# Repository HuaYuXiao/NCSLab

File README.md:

#  NCSLab 

## Installation

- Install [`Node.js`](https://nodejs.org/en/download/package-manager)

- Install [`three.js`](https://threejs.org/docs/index.html#manual/en/introduction/Installation) and a build tool [`Vite`](https://threejs.org/docs/index.html#manual/en/introduction/Installation)

## Launch

```bash
cd ~/NCSLab/workspace
python3 main.py
python3 mjpeg_server.py
```

### PWM波控制可变电源

输出电压与PWM波占空比关系如下：

参考：
- [PWM原理 PWM频率与占空比详解](https://blog.csdn.net/as480133937/article/details/103439546)

输出电流稳定在20mA。

## Picamera2

update:2024.6.14
下面这个方案已废弃

update:2024.5.17
先运行/src/online/Camera_test/server_camera.py 在localhost:8091/video_feed下开启视频流
然后/src/online/main.py 运行主网页

Reference
- ⭐️ https://github.com/barry-ran/raspberry-webcam
- ⭐️ [How to Install & Setup OpenCV on Raspberry Pi 4](https://how2electronics.com/how-to-install-setup-opencv-on-raspberry-pi-4)
- ⭐️ https://github.com/raspberrypi/picamera2/blob/main/examples/preview.py
- [Installing OpenCV on Raspberry Pi 4B](https://www.youtube.com/watch?v=OugQIz_vcFo)

## 识别电压电流数据

测试图片如下：

注意到，底色和内容颜色都是单一的，因此我们首先通过二值化将两者分离开来。

## Release Note

- v2.1.4:
    - fix issue #11 #12 #19
- v2.1.3: 
    - self defined `html` & `js`
- v2.1.2:
  - `rectangle-module` and `submit`
- v2.1.1:
  - support video streaming
- v2.1.0: 
  - support continuous channel switch
  - support check for invalid input

## Contributor
- Circuit Design: Xizhe Hao, Hongjin Tang
- Video Promotion：Zixuan zhong， Yuxiao Hua
- Web Design： Yuxiao Hua
- Patent Drafting: Yuxiao Hua, Xizhe Hao, Yifeng Zhang
- Patent Application:Xizhe Hao, Yuxiao Hua

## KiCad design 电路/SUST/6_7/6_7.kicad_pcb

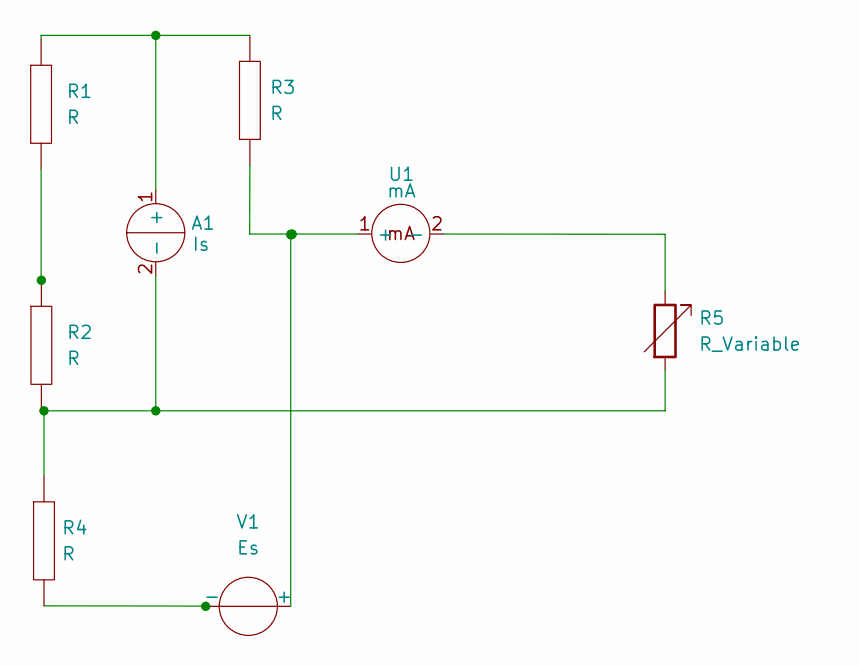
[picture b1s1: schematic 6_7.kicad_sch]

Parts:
A1: Is
R1, R2, R3, R4: R
R5: R_Variable; Rv
U1: mA; Multimeter
V1: Es; Vs

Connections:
unnamed: A1.1 (+), R1.1, R3.1
unnamed: A1.2 (-), R2.2, R4.1, R5.2
unnamed: R1.2, R2.1
unnamed: R3.2, U1.1 (+), V1.1 (+)
unnamed: R4.2, V1.2 (-)
unnamed: R5.1, U1.2 (-)

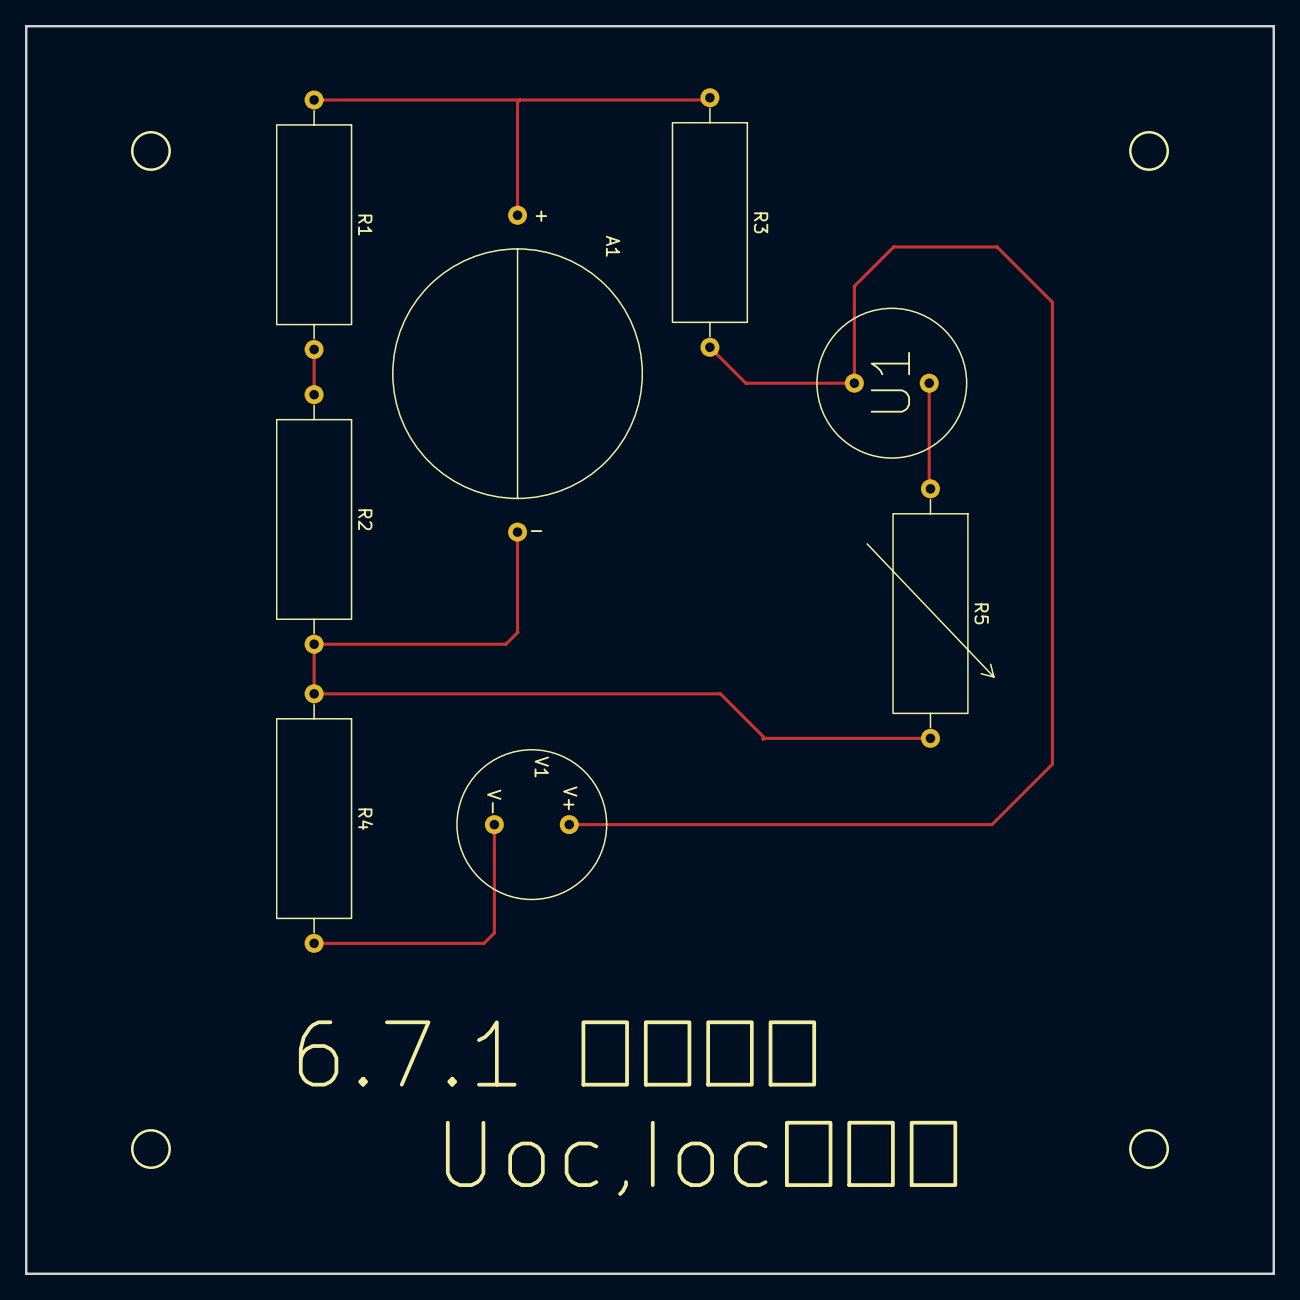
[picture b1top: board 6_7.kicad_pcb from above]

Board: 2 copper layers, 100.0 x 100.0 mm, 8 parts (0 on the bottom side), 6 nets.

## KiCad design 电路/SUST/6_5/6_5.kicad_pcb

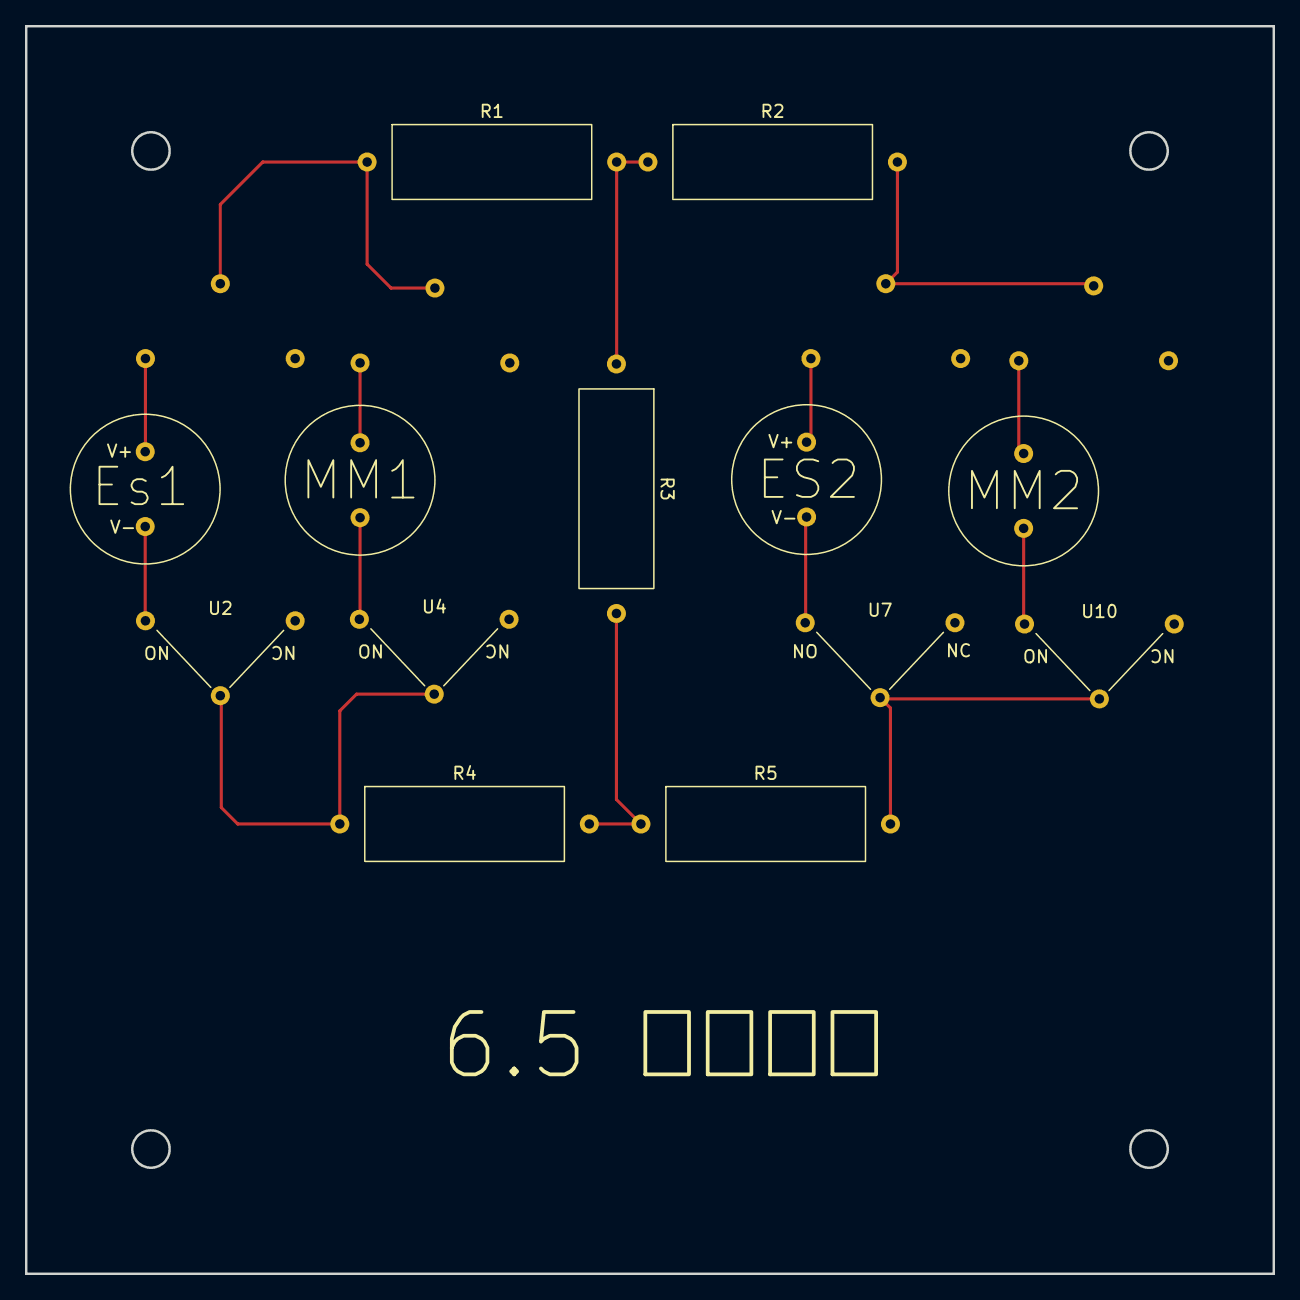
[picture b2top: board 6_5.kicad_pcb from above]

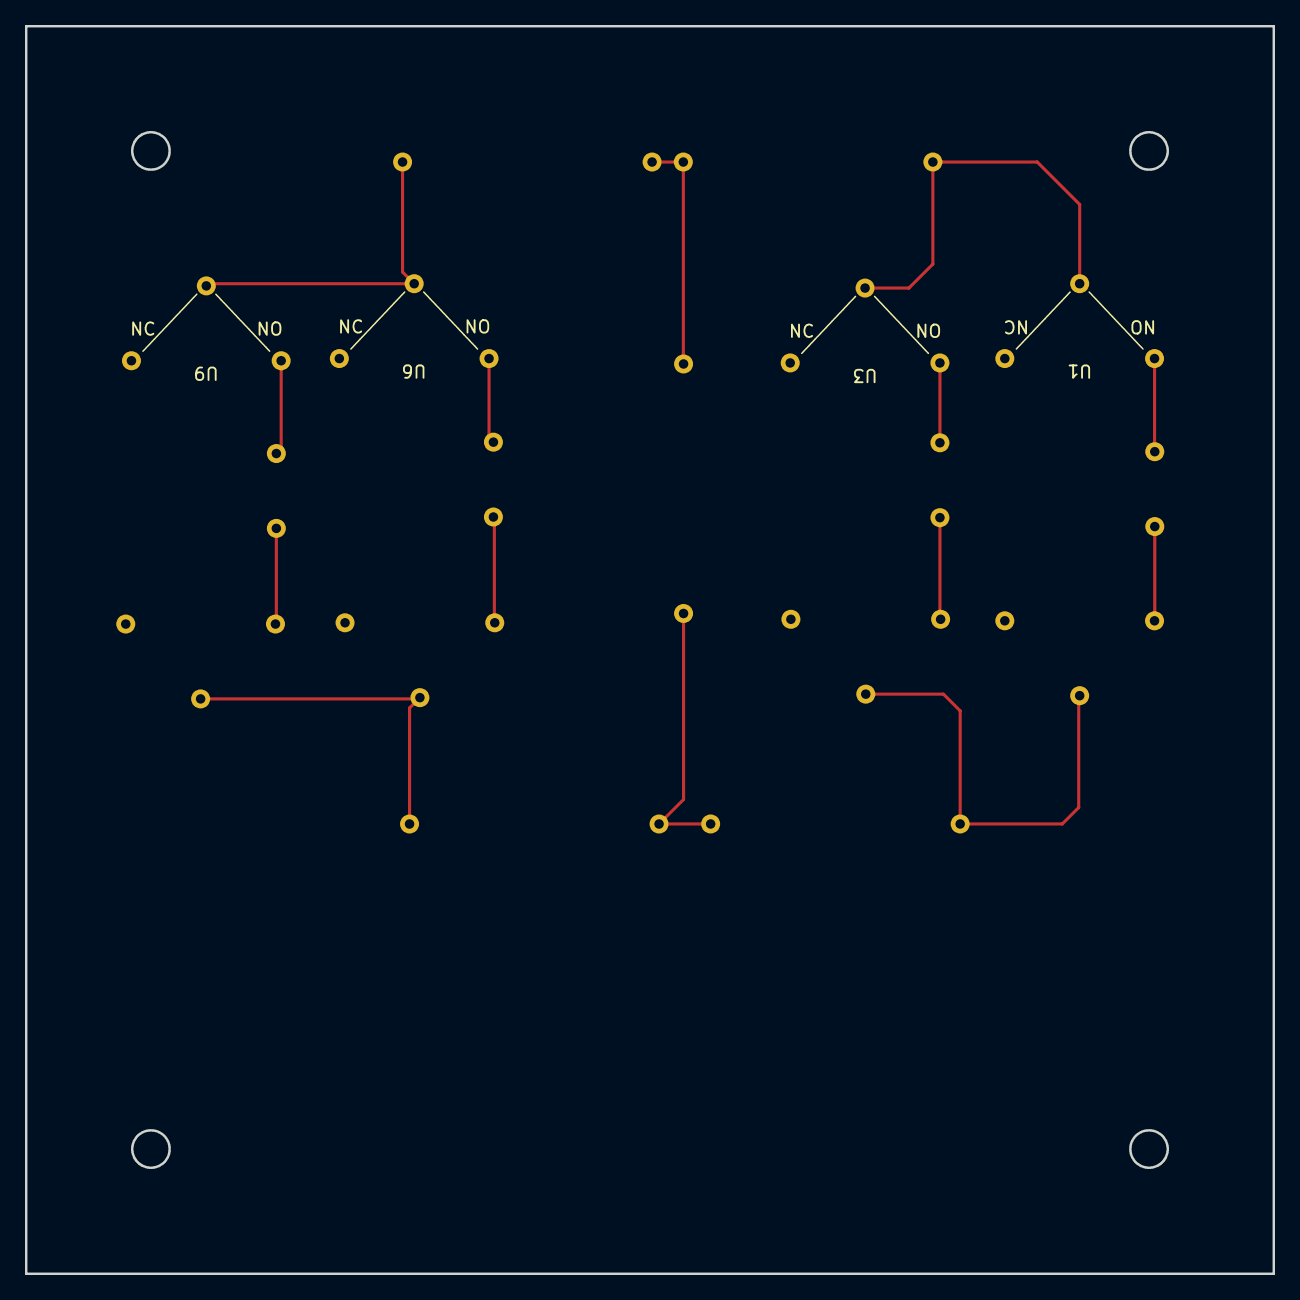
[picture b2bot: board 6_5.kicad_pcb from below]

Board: 2 copper layers, 100.0 x 100.0 mm, 17 parts (4 on the bottom side), 14 nets.

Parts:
ES2: Es; Vs
Es1: Es; Vs
MM1, MM2: Multimeter
R1, R3, R4: 510Ω; R
R2: 1kΩ; R
R5: 300Ω; R
U1, U2, U3, U4, U6, U7, U9, U10: Rly; RLy

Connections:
unnamed: R1.1, U1.1 (Com), U3.1 (Com)
unnamed: R1.2, R2.1, R3.1
unnamed: R2.2, U6.1 (Com), U9.1 (Com)
unnamed: R4.1, U2.1 (Com), U4.1 (Com)
unnamed: R3.2, R4.2, R5.1
unnamed: R5.2, U7.1 (Com), U10.1 (Com)
unnamed: Es1.1 (+), U1.3 (NO)
unnamed: Es1.2 (-), U2.3 (NO)
unnamed: MM1.1 (+), U3.3 (NO)
unnamed: MM1.2 (-), U4.3 (NO)
unnamed: ES2.1 (+), U6.3 (NO)
unnamed: ES2.2 (-), U7.3 (NO)
unnamed: MM2.1 (+), U9.3 (NO)
unnamed: MM2.2 (-), U10.3 (NO)

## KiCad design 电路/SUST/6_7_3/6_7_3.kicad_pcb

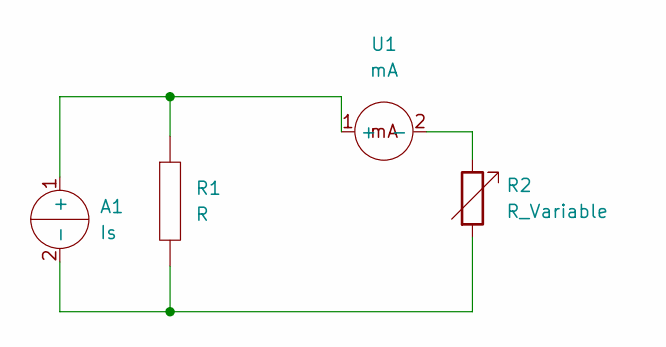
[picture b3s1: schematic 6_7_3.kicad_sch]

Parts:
A1: Is
R1: R
R2: R_Variable; Rv
U1: mA; Multimeter

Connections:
unnamed: A1.1 (+), R1.1, U1.1 (+)
unnamed: A1.2 (-), R1.2, R2.2
unnamed: R2.1, U1.2 (-)

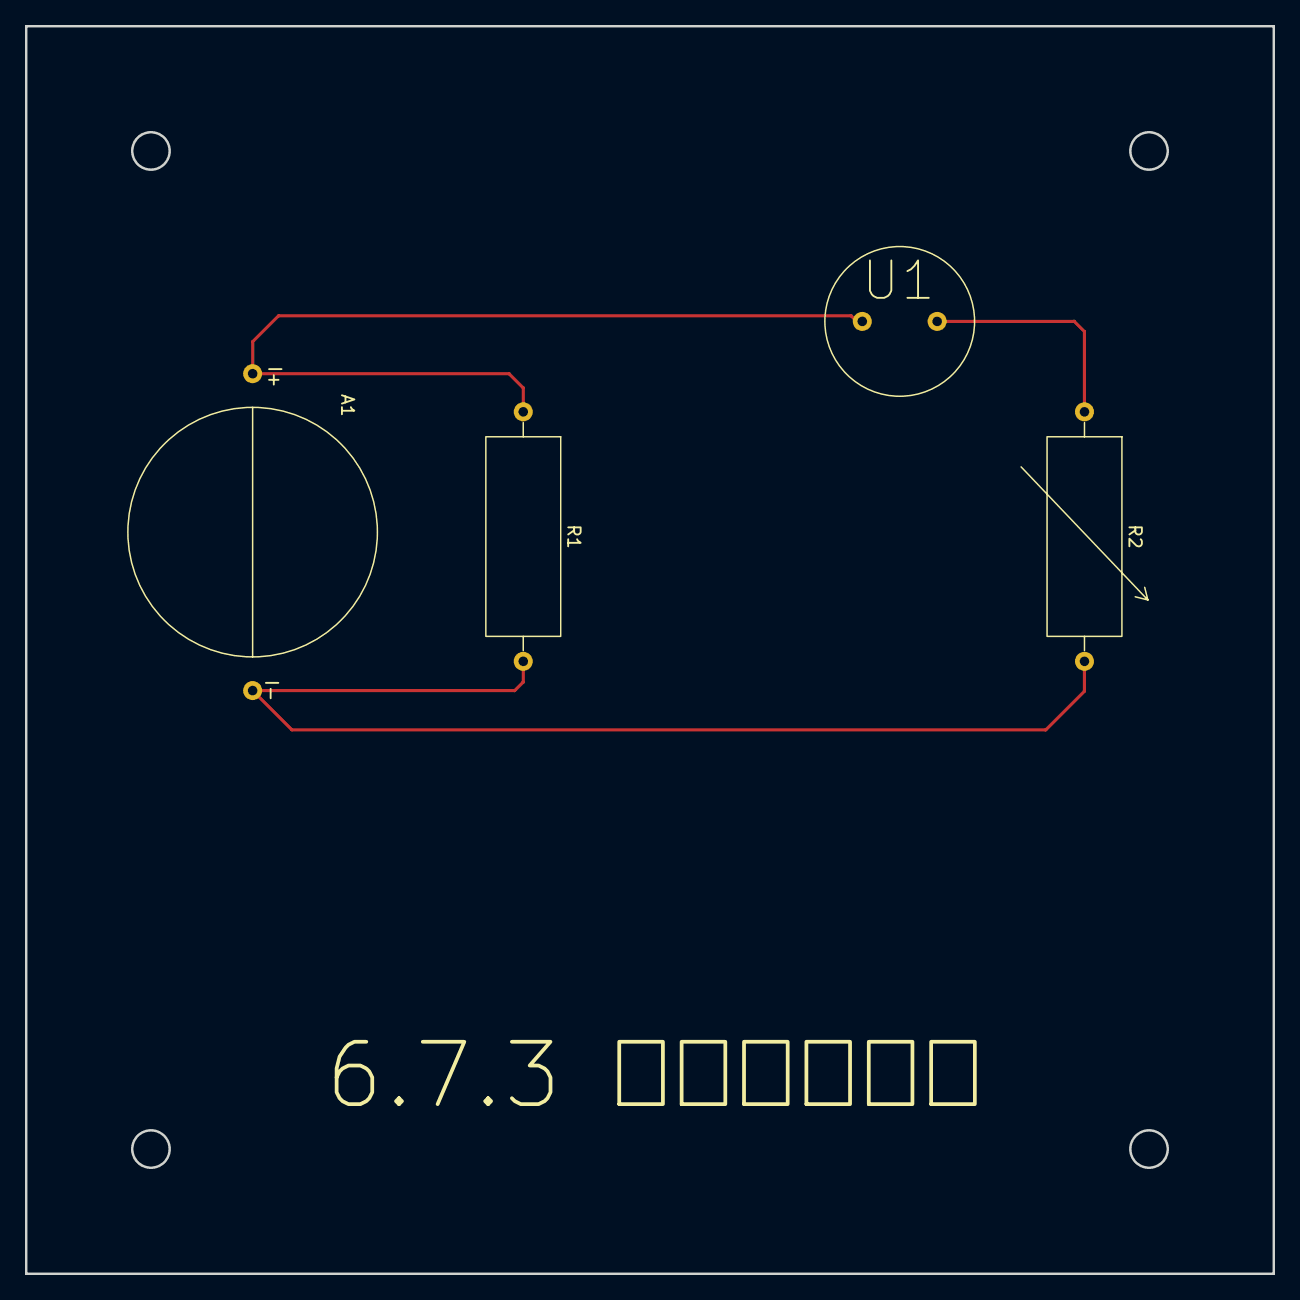
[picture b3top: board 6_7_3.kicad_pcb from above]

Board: 2 copper layers, 100.0 x 100.0 mm, 4 parts (0 on the bottom side), 3 nets.

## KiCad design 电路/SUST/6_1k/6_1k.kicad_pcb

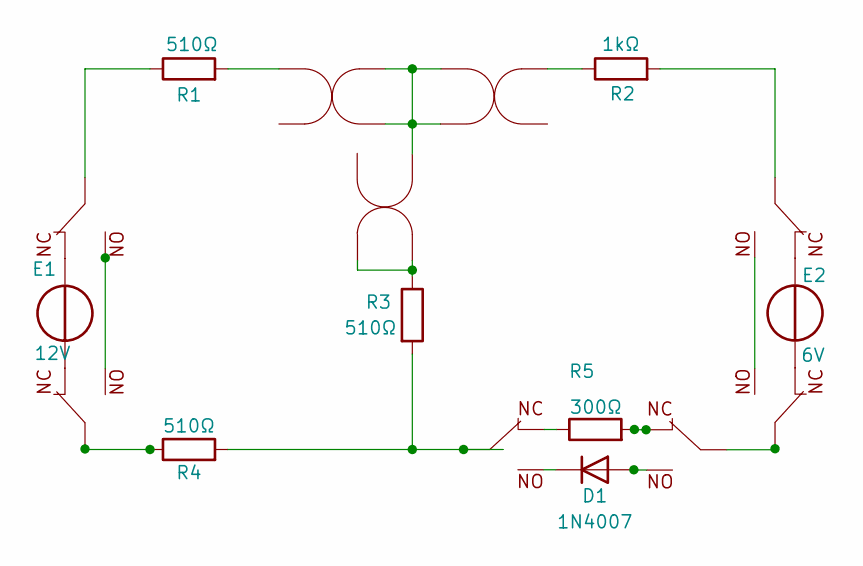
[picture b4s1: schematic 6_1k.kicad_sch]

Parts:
D1: 1N4007; D_DO-41_SOD81_P10.16mm_Horizontal
E1: 12V; Vs
E2: 6V; Vs
P1, P2, P3: AmPlug; ImaPlug
R1, R3, R4: 510Ω; R
R2: 1kΩ; R
R5: 300Ω; R
Rl1, Rl2, Rl3, Rl4, Rl5, Rl6: Relay; RLy

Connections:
unnamed: D1.2 (A), Rl2.3 (NO)
unnamed: E1.1 (V+), Rl3.2 (NC)
unnamed: E1.2 (V-), Rl4.2 (NC)
unnamed: E2.1 (V+), Rl5.3 (NC)
unnamed: E2.2 (V-), Rl6.3 (NC)
unnamed: P1.1, R1.2
unnamed: P1.3, P1.4, P2.3, P2.4, P3.3
unnamed: P2.1, R2.1
unnamed: P3.1, P3.2, R3.1
unnamed: R1.1, Rl3.1 (Com)
unnamed: R2.2, Rl5.1 (Com)
unnamed: R3.2, R4.2, Rl1.1 (Com)
unnamed: R4.1, Rl4.1 (Com)
unnamed: R5.1, Rl1.2 (NC)
unnamed: D1.1 (K), Rl1.3 (NO)
unnamed: R5.2, Rl2.2 (NC)
unnamed: Rl3.3 (NO), Rl4.3 (NO)
unnamed: Rl5.2 (NO), Rl6.2 (NO)
unnamed: Rl2.1 (Com), Rl6.1 (Com)

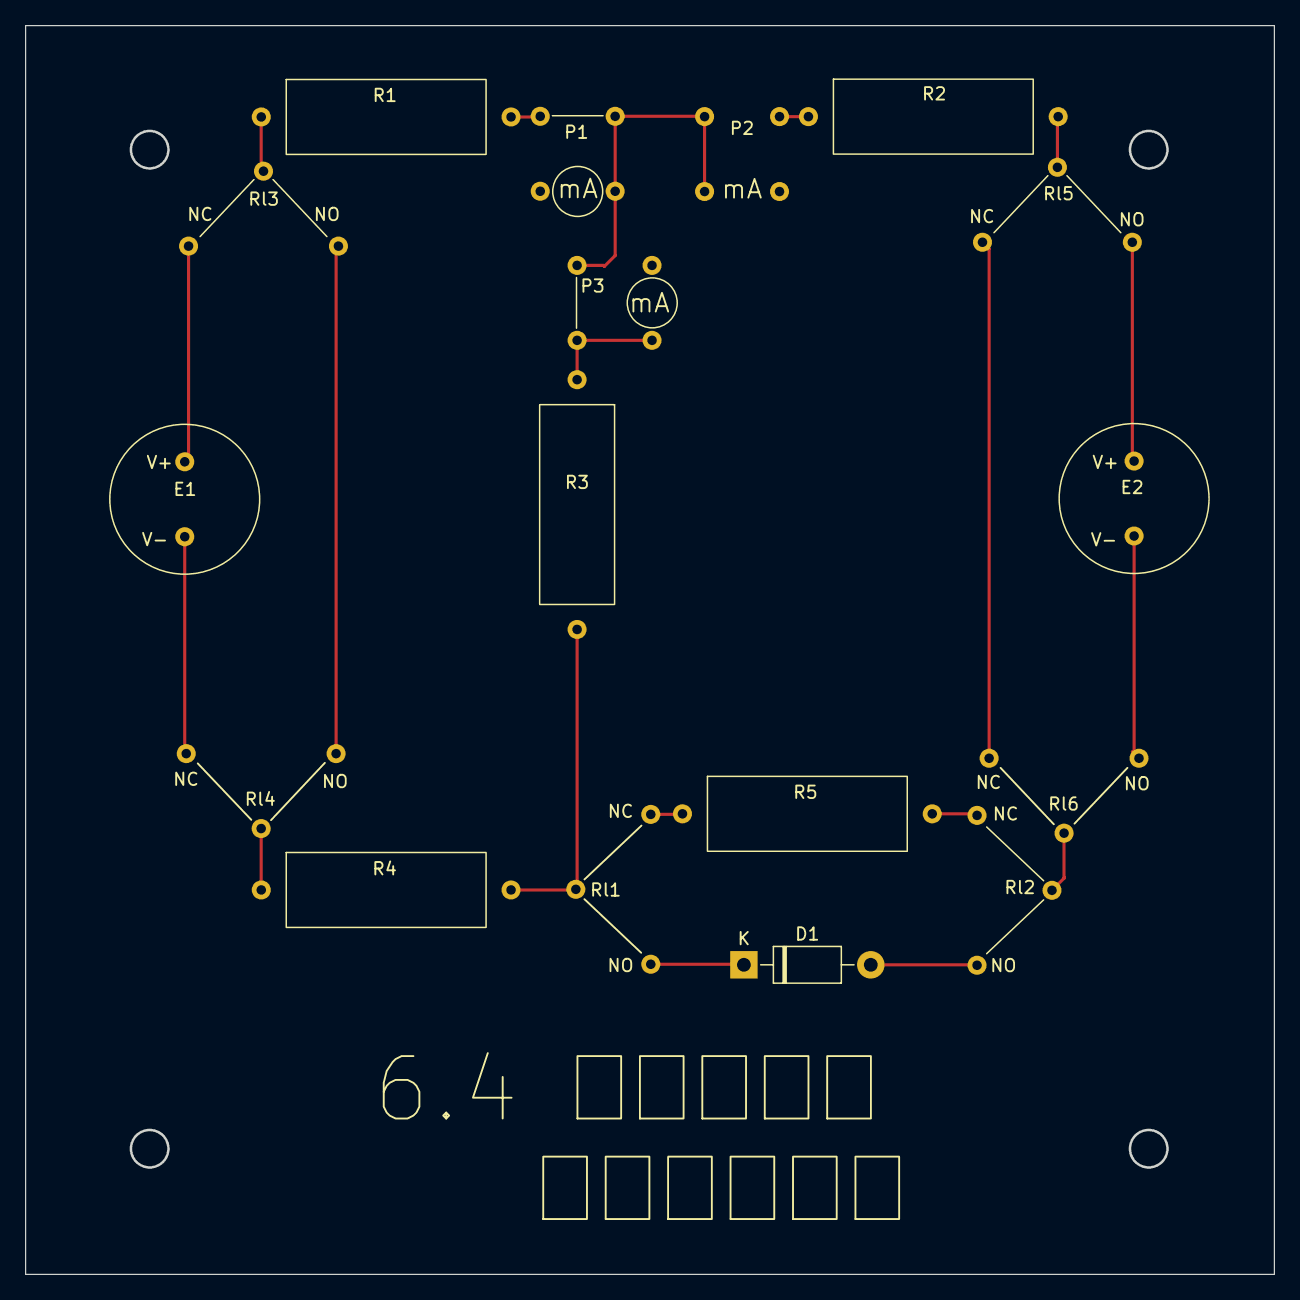
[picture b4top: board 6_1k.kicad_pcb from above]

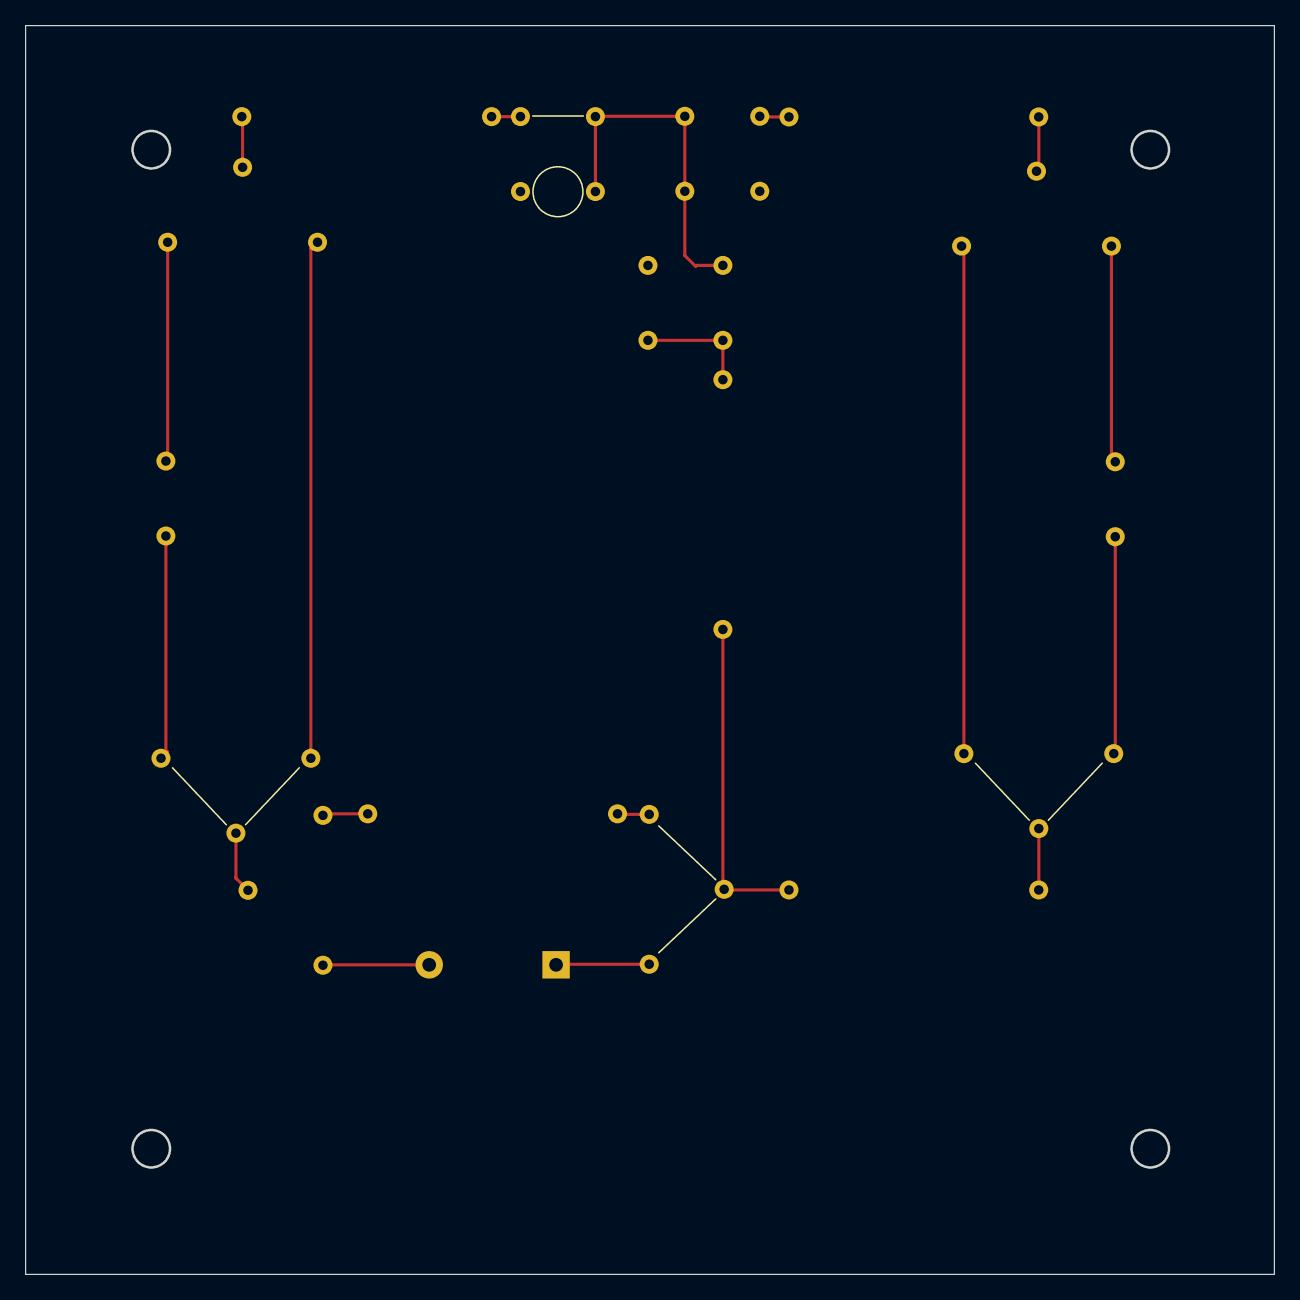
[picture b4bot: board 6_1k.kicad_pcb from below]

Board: 2 copper layers, 100.0 x 100.0 mm, 17 parts (4 on the bottom side), 19 nets.

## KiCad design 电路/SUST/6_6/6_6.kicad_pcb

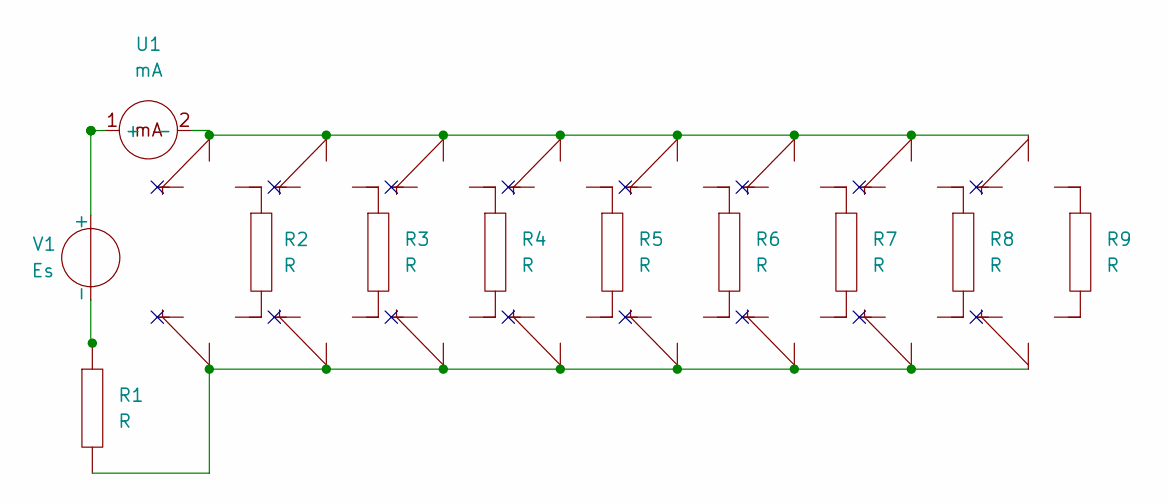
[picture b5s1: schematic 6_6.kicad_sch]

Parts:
R1, R2, R3, R4, R5, R6, R7, R8, R9: R
U1: mA; Multimeter
U2, U3, U4, U5, U6, U7, U8, U9, U10, U11, U12, U13, U14, U15, U16, U17: Rly; RLy
V1: Es; Vs

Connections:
unnamed: R3.1, U4.3 (NO)
unnamed: R3.2, U5.3 (NO)
unnamed: R6.2, U11.3 (NO)
unnamed: R8.1, U14.3 (NO)
unnamed: R9.1, U16.3 (NO)
unnamed: U1.1 (+), V1.1 (+)
unnamed: U1.2 (-), U2.1 (Com), U4.1 (Com), U6.1 (Com), U8.1 (Com), U10.1 (Com), U12.1 (Com), U14.1 (Com), U16.1 (Com)
unnamed: R2.1, U2.3 (NO)
unnamed: R1.2, U3.1 (Com), U5.1 (Com), U7.1 (Com), U9.1 (Com), U11.1 (Com), U13.1 (Com), U15.1 (Com), U17.1 (Com)
unnamed: R2.2, U3.3 (NO)
unnamed: R4.1, U6.3 (NO)
unnamed: R4.2, U7.3 (NO)
unnamed: R5.1, U8.3 (NO)
unnamed: R5.2, U9.3 (NO)
unnamed: R6.1, U10.3 (NO)
unnamed: R7.1, U12.3 (NO)
unnamed: R7.2, U13.3 (NO)
unnamed: R8.2, U15.3 (NO)
unnamed: R9.2, U17.3 (NO)
unnamed: R1.1, V1.2 (-)

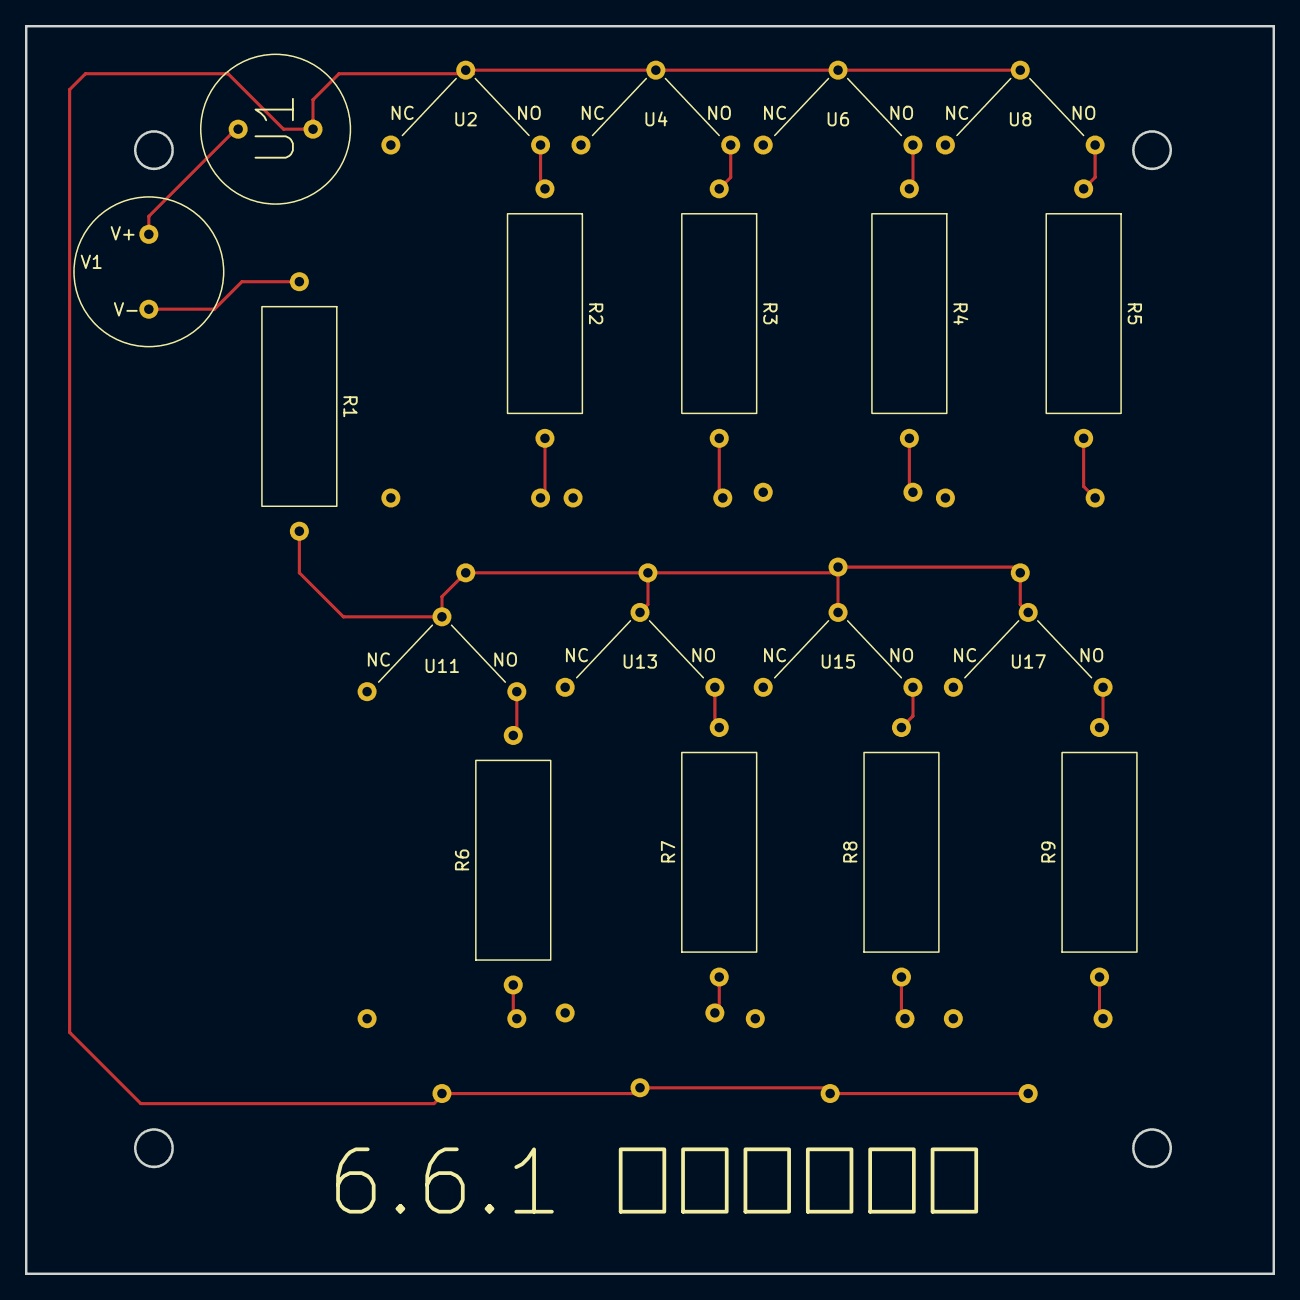
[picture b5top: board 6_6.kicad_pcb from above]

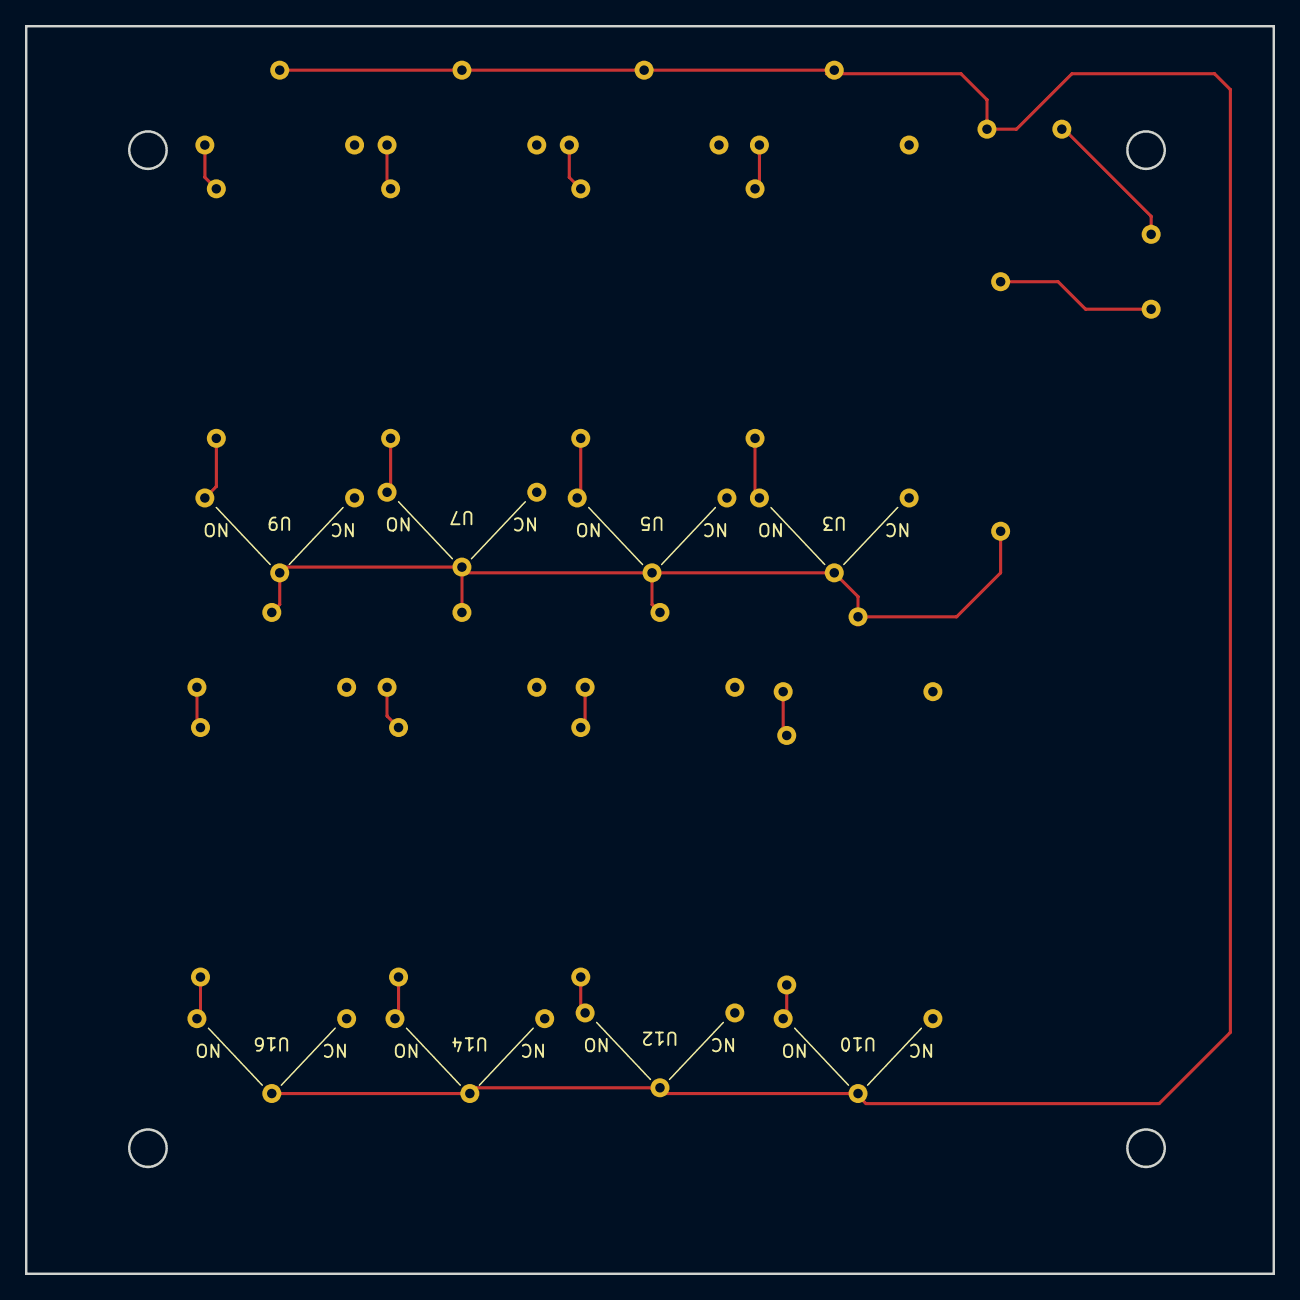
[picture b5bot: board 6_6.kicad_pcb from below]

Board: 2 copper layers, 100.0 x 100.0 mm, 27 parts (8 on the bottom side), 20 nets.

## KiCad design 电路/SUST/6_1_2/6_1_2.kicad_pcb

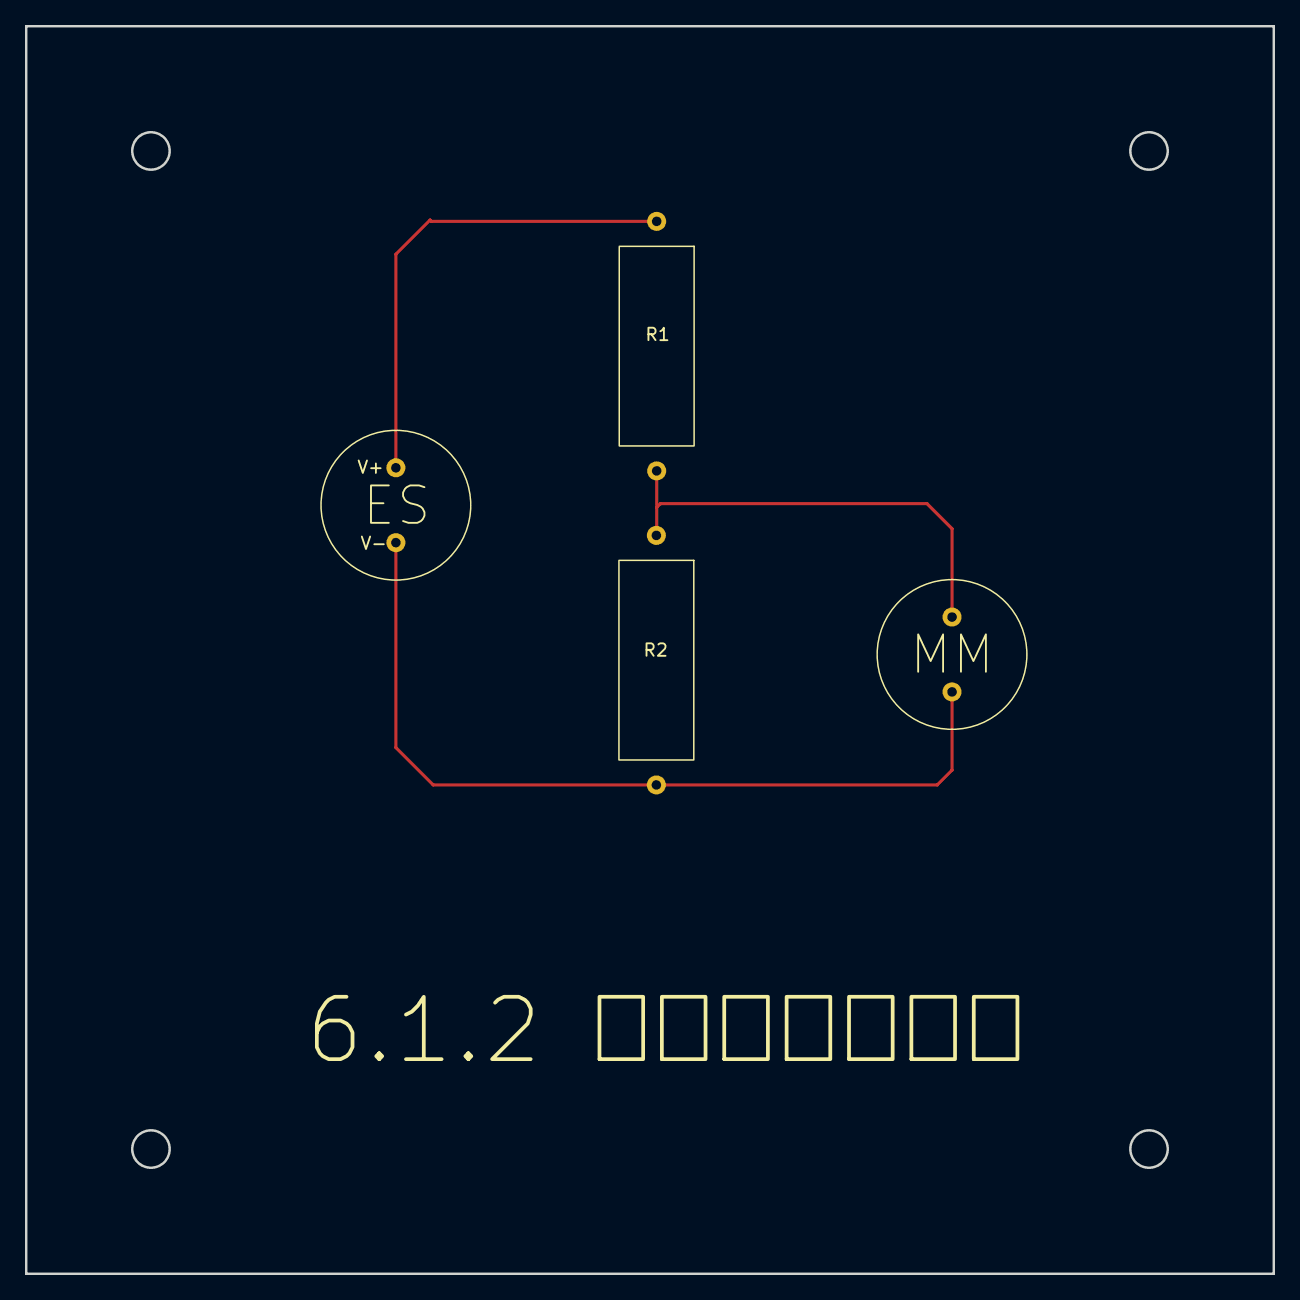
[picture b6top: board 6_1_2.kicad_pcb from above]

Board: 2 copper layers, 100.0 x 100.0 mm, 4 parts (0 on the bottom side), 3 nets.

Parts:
ES: 1V; Vs
MM: Multimeter
R1: 100kΩ; R
R2: 1.5MΩ; R

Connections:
unnamed: ES.1 (+), R1.1
unnamed: MM.1 (+), R1.2, R2.1
unnamed: ES.2 (-), MM.2 (-), R2.2

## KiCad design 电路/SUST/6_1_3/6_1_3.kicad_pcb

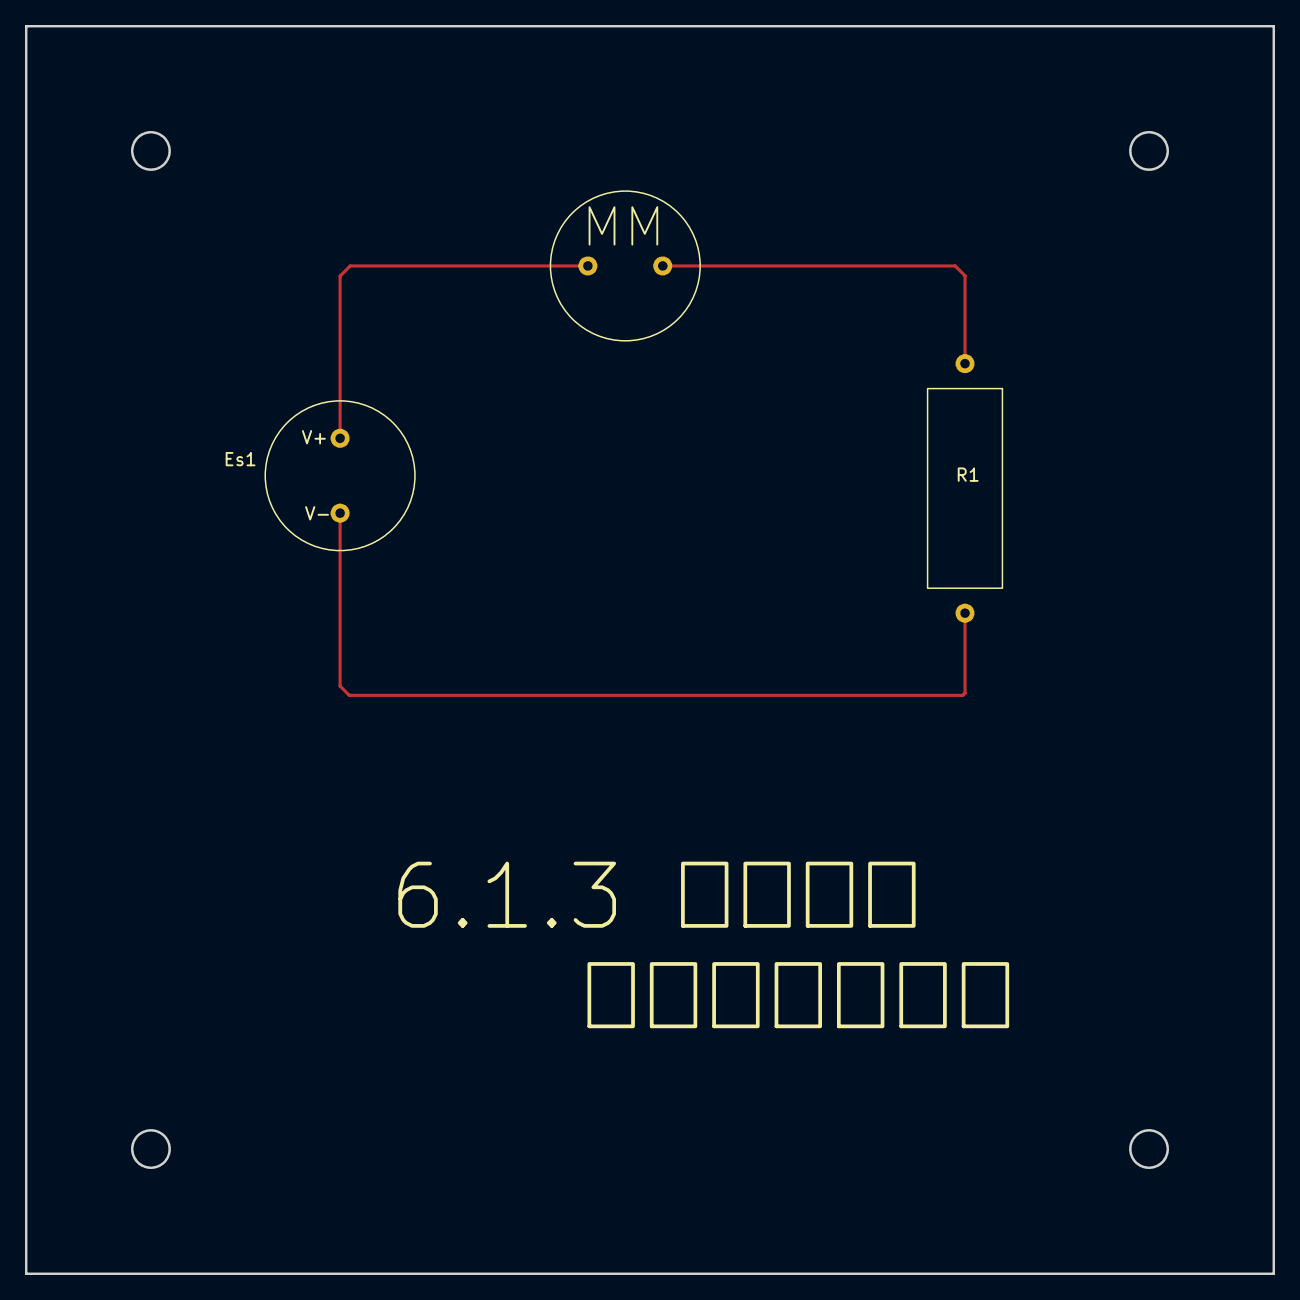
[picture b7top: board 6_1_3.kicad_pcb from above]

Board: 2 copper layers, 100.0 x 100.0 mm, 3 parts (0 on the bottom side), 3 nets.

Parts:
Es1: 1V; Vs
MM: mA; Multimeter
R1: 470kΩ; R

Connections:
unnamed: Es1.1 (+), MM.1 (+)
unnamed: Es1.2 (-), R1.2
unnamed: MM.2 (-), R1.1

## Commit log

2024-03-07 Upload
2024-03-07 Upload material
2024-03-08 Upload img
2024-03-09 Create 2023
2024-03-09 Someting about 挑战杯
2024-03-10 Implement output of PWM wave
2024-03-10 Upload files
2024-03-10 Derive relation between DUTY_CYCLE and Vout
2024-03-10 Complete class `PiCamera2`
2024-03-10 chdir
2024-03-10 Upload some img
2024-03-10 Upload note
2024-03-10 Update relation between `DUTY_CYCLE` and `Vout`
2024-03-13 Upload materials of PWM驱动板
2024-03-14 Update relation between `DUTY_CYCLE` and `Vout`.
2024-03-14 Add function of set duty_cycle and frequency
2024-03-14 Derive relationship of `Vout` to `DUTY_CYCLE`.
2024-03-14 Update something about camera.
2024-03-14 Binarize the raw image
2024-03-30 Upload logs
2024-03-30 Camera
2024-03-30 Server issue #9
2024-03-30 not sloved issue #11
2024-03-30 server for pwm
2024-03-30 able to set pwm
2024-03-30 check input, ensure it is a number
2024-03-31 main
2024-04-14 [New] Camera online transfer
2024-04-14 [Update] Combine camera and PWM
2024-04-14 [Update] Configure home page
2024-04-14 [Update] Update home page
2024-05-14 PWM version
2024-05-15 [update | pass]
2024-05-16 [update | pass] support continuous channel switch
2024-05-17 [update | pass] add `rectangle-module`
2024-05-17 [update | pass] self defined `html` & `js`
2024-05-18 [update | pass] upload reference
2024-06-04 [issue | #19 | v2.1.1] merge input and camera
2024-06-10 Create USB_Camera
2024-06-10 Rename USB_Camera to USB_Camera.py
2024-06-10 [update | fail | v2.1.2] update camera
2024-06-14 [update | pass | v2.1.4] fix issue #11 #12 #19
2024-06-14 [update | fail | v2.2.0]
2024-06-15 [update | pass | v2.2.0] load model from online source
2024-06-15 [update | pass | v2.2.0] load model from offline source
2024-06-15 [update | pass | v2.2.0] load model on website
2024-06-22 实物原图
2024-07-02 something about 攀登计划
